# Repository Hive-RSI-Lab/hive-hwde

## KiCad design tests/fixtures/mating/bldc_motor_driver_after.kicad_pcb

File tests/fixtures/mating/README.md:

Frozen boards for `tests/test_mating.py`: the owner's two boards whose
connectors could not be mated, each before and after its fix, so the
mating check is tested on real footprints without reading the live boards
repo.

| file | boards repo commit | board |
|---|---|---|
| `lipo_boost_before` | `bd99e487` | PCB-0021-A lipo-boost, J4 USB-A mouth into the board |
| `lipo_boost_after` | `8eb0280b` (#19) | same, J4 turned to face the edge |
| `bldc_motor_driver_before` | `42e9af76` | PCB-0018-A bldc-motor-driver, J701/J702 mouths into the board |
| `bldc_motor_driver_after` | `91e76be2` (#22) | same, J701/J702 turned to face the edge |

Each is trimmed to the header, the Edge.Cuts outline and a few footprints:
lipo-boost keeps J2, J4 and L1 (the inductor in front of J4's old mouth);
bldc-motor-driver keeps J601, J701, J702, F701 and U301 (one part in front
of each old mouth). Tracks, zones and every other part are dropped, and 3D
model paths are rewritten to `${KIPRJMOD}/lib/aiee.3dshapes/<name>`. Do not
regenerate them; the tests pin what they flag.

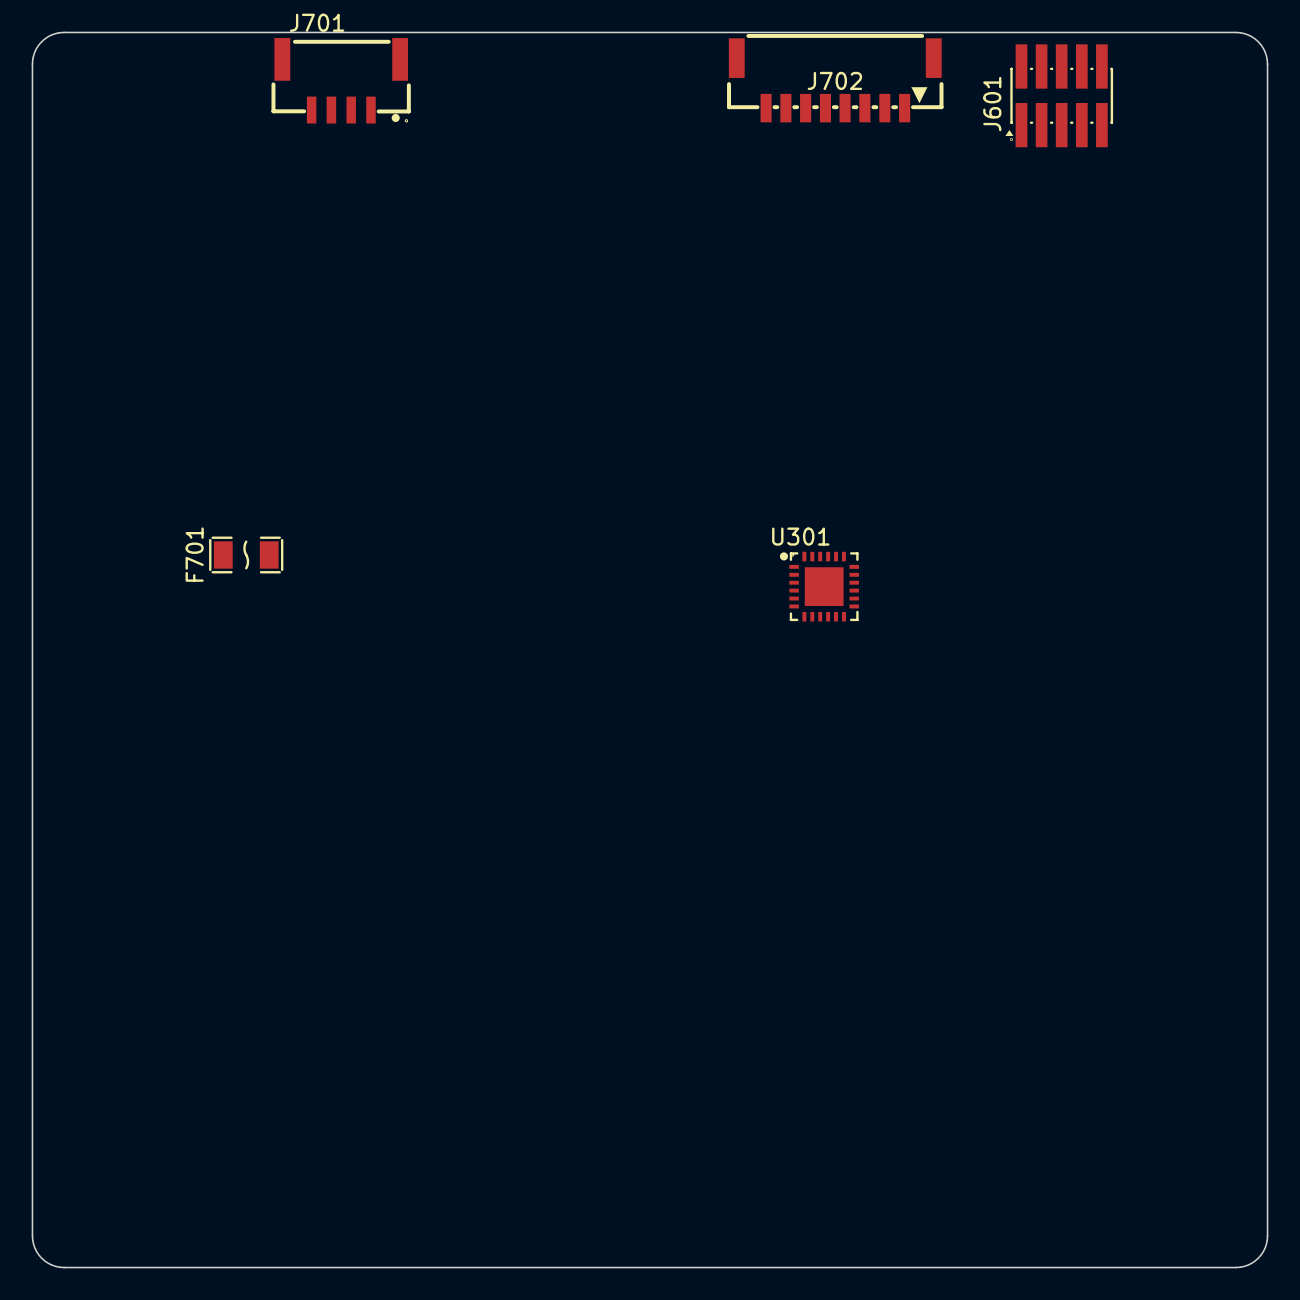
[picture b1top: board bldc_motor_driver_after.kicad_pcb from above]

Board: 4 copper layers, 78.0 x 78.0 mm, 5 parts (0 on the bottom side), 2 nets, no tracks yet.

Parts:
F701: PTC 0.2A hold 30V; F1206
J601: SWD 2x5 1.27mm; CONN-SMD_10P-P1.27_XFCN_PZ127VS-12-10-H10-A38
J701: JST-GH 4p SMD; CONN-SMD_4P-P1.25_SM04B-GHS-TB-LF-SN
J702: JST-GH 8p SMD; CONN-SMD_SH-SM08B-GHS-TB
U301: DRV8300DRGER; VQFN-24_L4.0-W4.0-P0.50-TL-EP2.5

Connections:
/io/CTL_5V: F701.2, J701.2
GND: J601.3, J601.5, J601.9, J701.1, J702.2, U301.6, U301.7, U301.8, U301.25

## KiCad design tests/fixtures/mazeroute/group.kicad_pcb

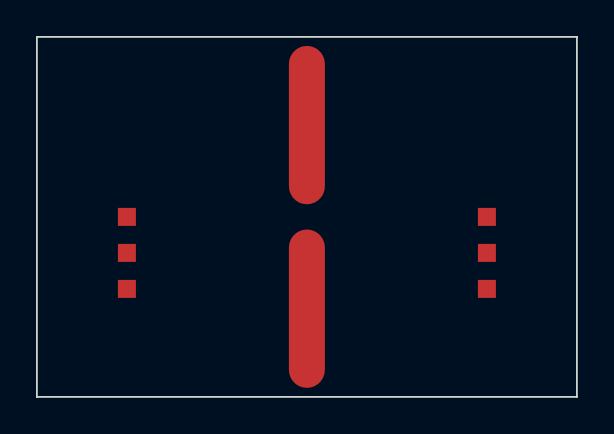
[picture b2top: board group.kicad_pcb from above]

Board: 2 copper layers, 30.0 x 20.0 mm, 6 parts (0 on the bottom side), 3 nets.

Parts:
A1: A1
A2: A2
B1: B1
B2: B2
C1: C1
C2: C2

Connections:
A: A1.1, A2.1
B: B1.1, B2.1
C: C1.1, C2.1
